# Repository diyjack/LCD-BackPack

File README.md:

# LCD-BackPack
Backpack to control HD44780 compatible displays over UART or I2C.

## Shop
* [LCD-BackPack](http://www.watterott.com/en/LCD-BackPack)

## Features
* Atmel AVR ATmega328 @ 16 MHz (external resonator)
* Arduino Bootloader (optiboot) with auto baud rate detection
* Serial (UART) and I2C interface
* Single LED and RGB LED backlight support (dimmable)
* Compatible with [SparkFun SerLCD](https://github.com/sparkfun/Serial_Enabled_LCD_Backpack)

## Hardware and Software
* [Schematics + Layout](https://github.com/watterott/LCD-BackPack/tree/master/pcb)
* [Arduino Firmware/Example](https://github.com/watterott/Arduino-Libs/tree/master/LCD_BackPack/examples/SerLCD)

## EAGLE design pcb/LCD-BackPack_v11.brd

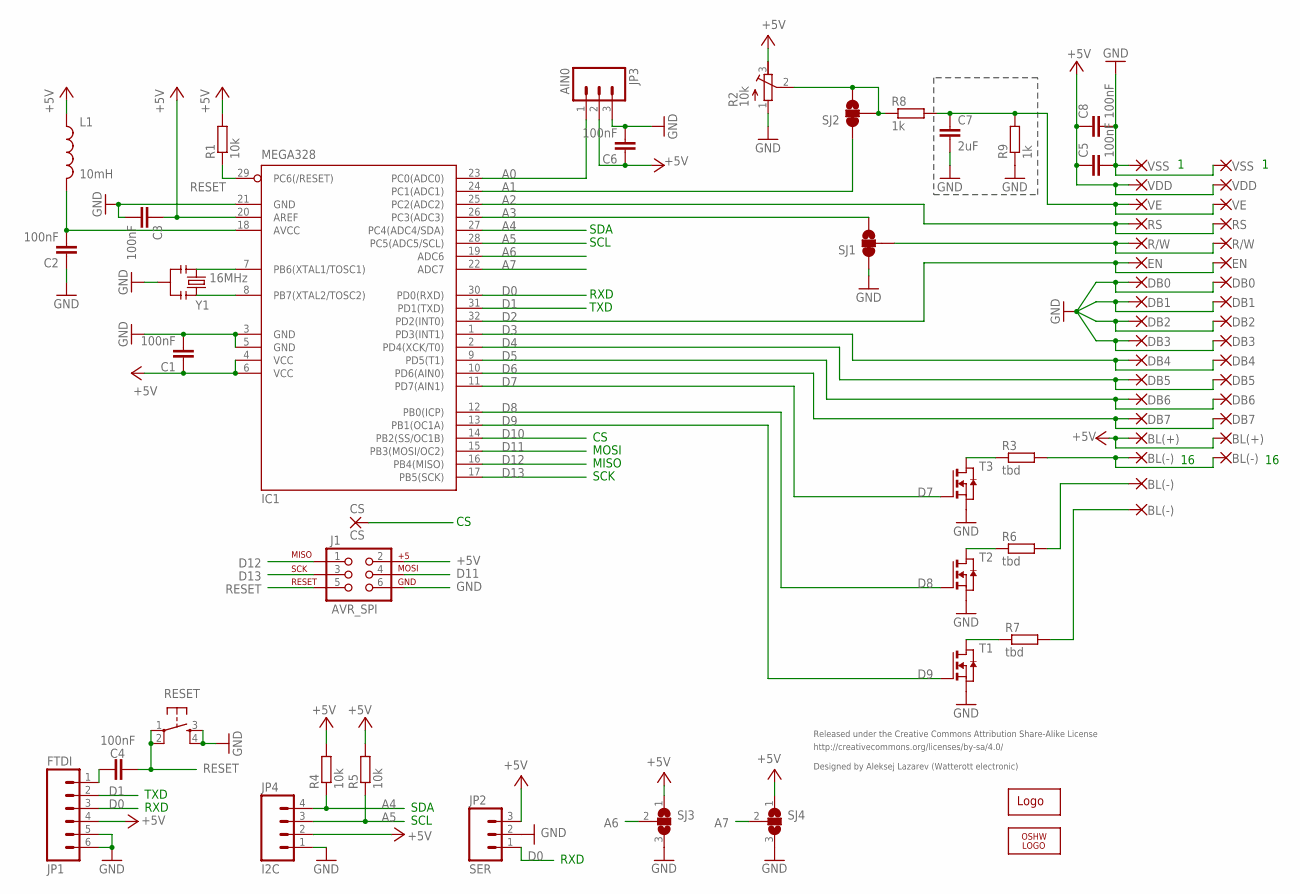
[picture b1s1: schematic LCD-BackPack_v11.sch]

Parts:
C1, C2, C3, C4, C5, C6, C8: 100nF; C0603
C7: 2uF; C0603
CS: CS; 1,6/0,9
IC1: MEGA328; TQFP32-08
J1: AVR_SPI; 2X3
JP1: FTDI; 1X06
JP2: SER; 1X03
JP3: AIN0; 1X03
JP4: I2C; 1X04
L1: 10mH; 0603
LOGO1: OSHW_LOGO_6MILX0150-NT; OSHW_6X150_NOTEXT
P1, P19: VSS; 1,6/0,9
P2, P20: VDD; 1,6/0,9
P3, P21: VE; 1,6/0,9
P4, P22: RS; 1,6/0,9
P5, P23: R/W; 1,6/0,9
P6, P24: EN; 1,6/0,9
P7, P25: DB0; 1,6/0,9
P8, P26: DB1; 1,6/0,9
P9, P27: DB2; 1,6/0,9
P10, P28: DB3; 1,6/0,9
P11, P29: DB4; 1,6/0,9
P12, P30: DB5; 1,6/0,9
P13, P31: DB6; 1,6/0,9
P14, P32: DB7; 1,6/0,9
P15, P33: BL(+); 1,6/0,9
P16, P17, P18, P34: BL(-); 1,6/0,9
R1, R4, R5: 10k; R0603
R2: 10k; RTRIM3374
R3, R6, R7: tbd; R0603
R8, R9: 1k; R0603
RESET: TAC_SWITCHSMD; TACTILE_SWITCH_SMD
SJ1, SJ2: SOLDERJUMPER_2WAY-OLDS; SJ_3
SJ3, SJ4: SJ2W; SJ_2
T1, T2, T3: NMOSSOT23; SOT-23
U$1: WE-LOGO
Y1: 16MHz; RESONATOR-SMD

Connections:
+5V: C1.1, C3.1, C5.1, C6.1, C8.1, IC1.4 (VCC), IC1.6 (VCC), IC1.20 (AREF), J1.2, JP1.4, JP2.3, JP3.2, JP4.2, L1.1, P2.1, P15.1, P20.1, P33.1, R1.2, R2.3 (A), R4.2, R5.2, SJ3.1, SJ4.1
A0: IC1.23 (PC0(ADC0)), JP3.1
A1: IC1.24 (PC1(ADC1)), SJ2.1
A2: IC1.25 (PC2(ADC2)), P4.1, P22.1
A3: IC1.26 (PC3(ADC3)), SJ1.3
A4: IC1.27 (PC4(ADC4/SDA)), JP4.4, R4.1
A5: IC1.28 (PC5(ADC5/SCL)), JP4.3, R5.1
A6: IC1.19 (ADC6), SJ3.2
A7: IC1.22 (ADC7), SJ4.2
AVCC: C2.2, IC1.18 (AVCC), L1.2
D0: IC1.30 (PD0(RXD)), JP1.3, JP2.1
D1: IC1.31 (PD1(TXD)), JP1.2
D2: IC1.32 (PD2(INT0)), P6.1, P24.1
D3: IC1.1 (PD3(INT1)), P11.1, P29.1
D4: IC1.2 (PD4(XCK/T0)), P12.1, P30.1
D5: IC1.9 (PD5(T1)), P13.1, P31.1
D6: IC1.10 (PD6(AIN0)), P14.1, P32.1
D7: IC1.11 (PD7(AIN1)), T3.3 (G)
D8: IC1.12 (PB0(ICP)), T2.3 (G)
D9: IC1.13 (PB1(OC1A)), T1.3 (G)
D10: CS.1, IC1.14 (PB2(SS/OC1B))
D11: IC1.15 (PB3(MOSI/OC2)), J1.4
D12: IC1.16 (PB4(MISO)), J1.1
D13: IC1.17 (PB5(SCK)), J1.3
GND: C1.2, C2.1, C3.2, C5.2, C6.2, C7.2, C8.2, IC1.3 (GND), IC1.5 (GND), IC1.21 (GND), J1.6, JP1.5, JP1.6, JP2.2, JP3.3, JP4.1, P1.1, P7.1, P8.1, P9.1, P10.1, P19.1, P25.1, P26.1, P27.1, P28.1, R2.1 (E), R9.1, RESET.3, RESET.4, SJ1.1, SJ3.3, SJ4.3, T1.2 (S), T2.2 (S), T3.2 (S), Y1.2
unnamed: R6.1, T2.1 (D)
unnamed: P18.1, R7.2
unnamed: C4.2, JP1.1
unnamed: R3.1, T3.1 (D)
unnamed: P17.1, R6.2
unnamed: R7.1, T1.1 (D)
unnamed: P16.1, P34.1, R3.2
RESET: C4.1, IC1.29 (PC6(/RESET)), J1.5, R1.1, RESET.1, RESET.2
RW: P5.1, P23.1, SJ1.2
VE: C7.1, P3.1, P21.1, R8.2, R9.2
VPOT: R2.2 (S), R8.1, SJ2.2, SJ2.3
XTAL1: IC1.7 (PB6(XTAL1/TOSC1)), Y1.1
XTAL2: IC1.8 (PB7(XTAL2/TOSC2)), Y1.3

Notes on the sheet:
MOSI
MISO
SCK
TXD
RXD
SCL
SDA
Released under the Creative Commons Attribution Share-Alike License
http://creativecommons.org/licenses/by-sa/4.0/
Designed by Aleksej Lazarev (Watterott electronic)

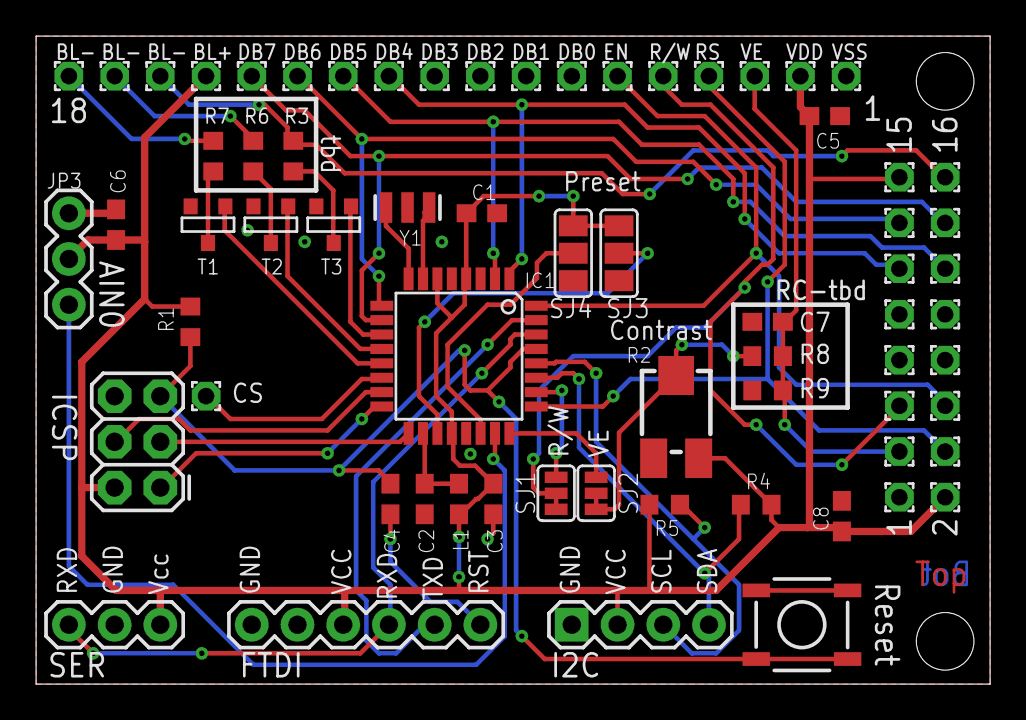
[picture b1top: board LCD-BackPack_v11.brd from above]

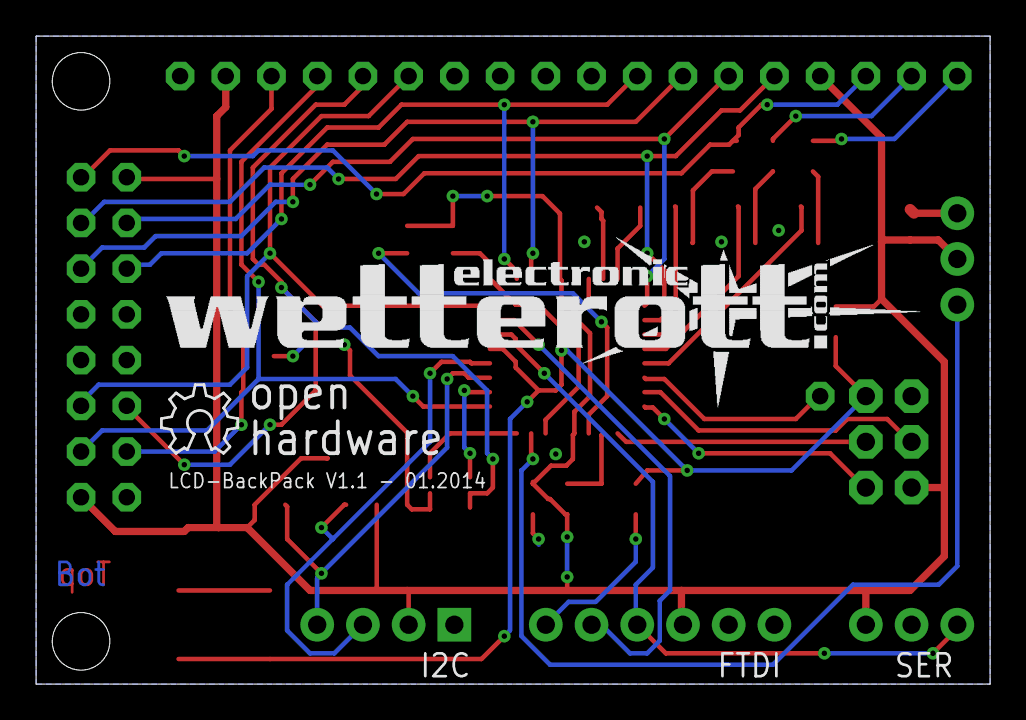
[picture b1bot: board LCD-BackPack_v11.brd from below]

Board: 2 copper layers, 53.0 x 36.0 mm, 70 parts (2 on the bottom side), 38 nets.

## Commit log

2014-03-10 added readme
2014-03-10 added schematics and layout files
2014-03-13 added image
2014-08-21 updated layout and schematics
2014-11-06 cleaned up schematics and layout
2015-01-10 moved image

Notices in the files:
parts and their libraries:
SparkFun-FreqCtrl: Licensing: CC v3.0 Share-Alike You are welcome to use this library for commercial purposes.
